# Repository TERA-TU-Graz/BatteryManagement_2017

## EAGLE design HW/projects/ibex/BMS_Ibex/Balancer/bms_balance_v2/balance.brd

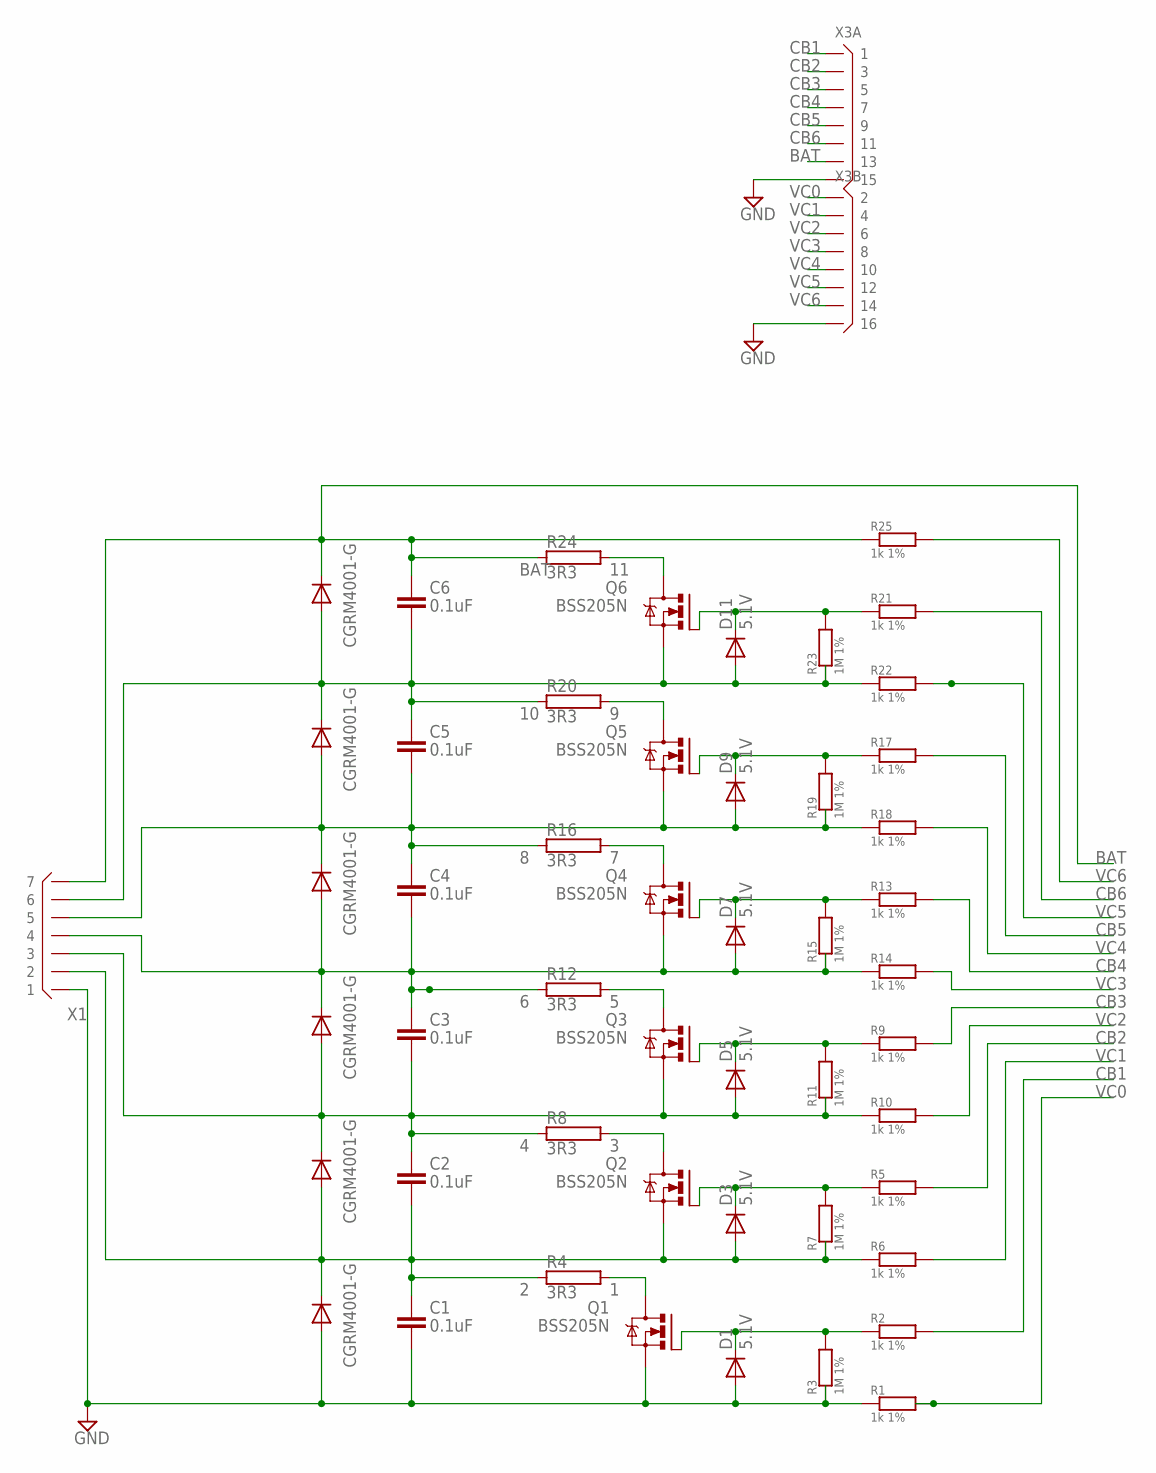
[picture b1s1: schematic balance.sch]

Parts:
C1, C2, C3, C4, C5, C6: 0.1uF; C0805
D1, D3, D5, D7, D9, D11: 5.1V; SOD-323
D2, D4, D6, D8, D10, D12: CGRM4001-G; SOD-123_MINI-SMA
Q1, Q2, Q3, Q4, Q5, Q6: BSS205N; SOT23
R1, R2, R5, R6, R9, R10, R13, R14, R17, R18, R21, R22, R25: 1k 1%; R0805
R3, R7, R11, R15, R19, R23: 1M 1%; R0805
R4, R8, R12, R16, R20, R24: 3R3; HS15
X1: B7B-XH
X3: X08X2DR; X16R-DIL

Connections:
1: Q1.3 (D), R4.2
2: C1.2, C2.1, D2.C, D3.2 (A), D4.A, Q2.2 (S), R4.1, R6.1, R7.1, X1.P$2 (2)
3: Q2.3 (D), R8.2
4: C2.2, C3.1, D4.C, D5.2 (A), D6.A, Q3.2 (S), R8.1, R10.1, R11.1, X1.P$3 (3)
5: Q3.3 (D), R12.2
6: C3.2, C4.1, D6.C, D7.2 (A), D8.A, Q4.2 (S), R12.1, R14.1, R15.1, X1.P$4 (4)
7: Q4.3 (D), R16.2
8: C4.2, C5.1, D8.C, D9.2 (A), D10.A, Q5.2 (S), R16.1, R18.1, R19.1, X1.P$5 (5)
9: Q5.3 (D), R20.2
10: C5.2, C6.1, D10.C, D11.2 (A), D12.A, Q6.2 (S), R20.1, R22.1, R23.1, X1.P$6 (6)
11: Q6.3 (D), R24.2
BAT: C6.2, D12.C, R24.1, R25.1, X1.P$7 (7), X3.13
CB1: R2.2, X3.1
CB2: R5.2, X3.3
CB3: R9.2, X3.5
CB4: R13.2, X3.7
CB5: R17.2, X3.9
CB6: R21.2, X3.11
GND: C1.1, D1.2 (A), D2.A, Q1.2 (S), R1.1, R3.1, X1.P$1 (1), X3.15, X3.16
unnamed: D1.1 (C), Q1.1 (G), R2.1, R3.2
unnamed: D3.1 (C), Q2.1 (G), R5.1, R7.2
unnamed: D5.1 (C), Q3.1 (G), R9.1, R11.2
unnamed: D7.1 (C), Q4.1 (G), R13.1, R15.2
unnamed: D9.1 (C), Q5.1 (G), R17.1, R19.2
unnamed: D11.1 (C), Q6.1 (G), R21.1, R23.2
VC0: R1.2, X3.2
VC1: R6.2, X3.4
VC2: R10.2, X3.6
VC3: R14.2, X3.8
VC4: R18.2, X3.10
VC5: R22.2, X3.12
VC6: R25.2, X3.14

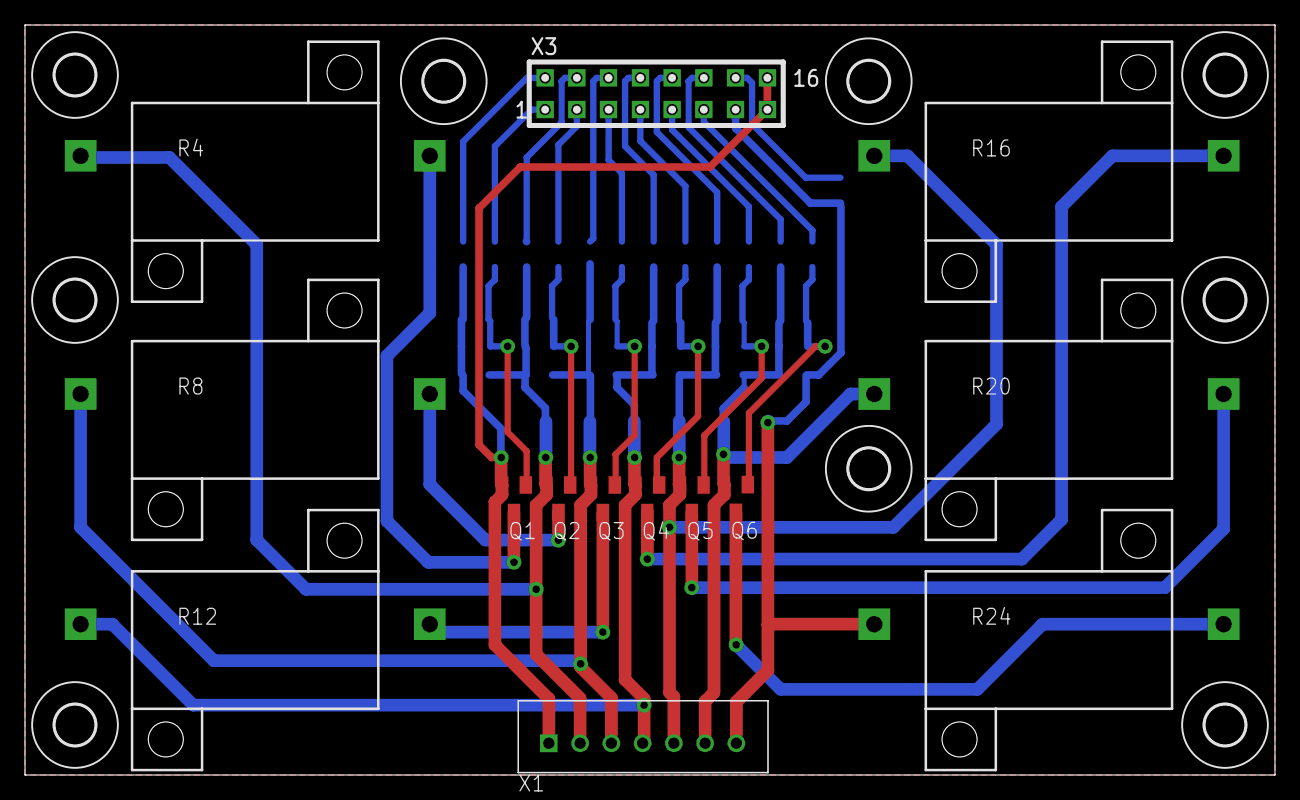
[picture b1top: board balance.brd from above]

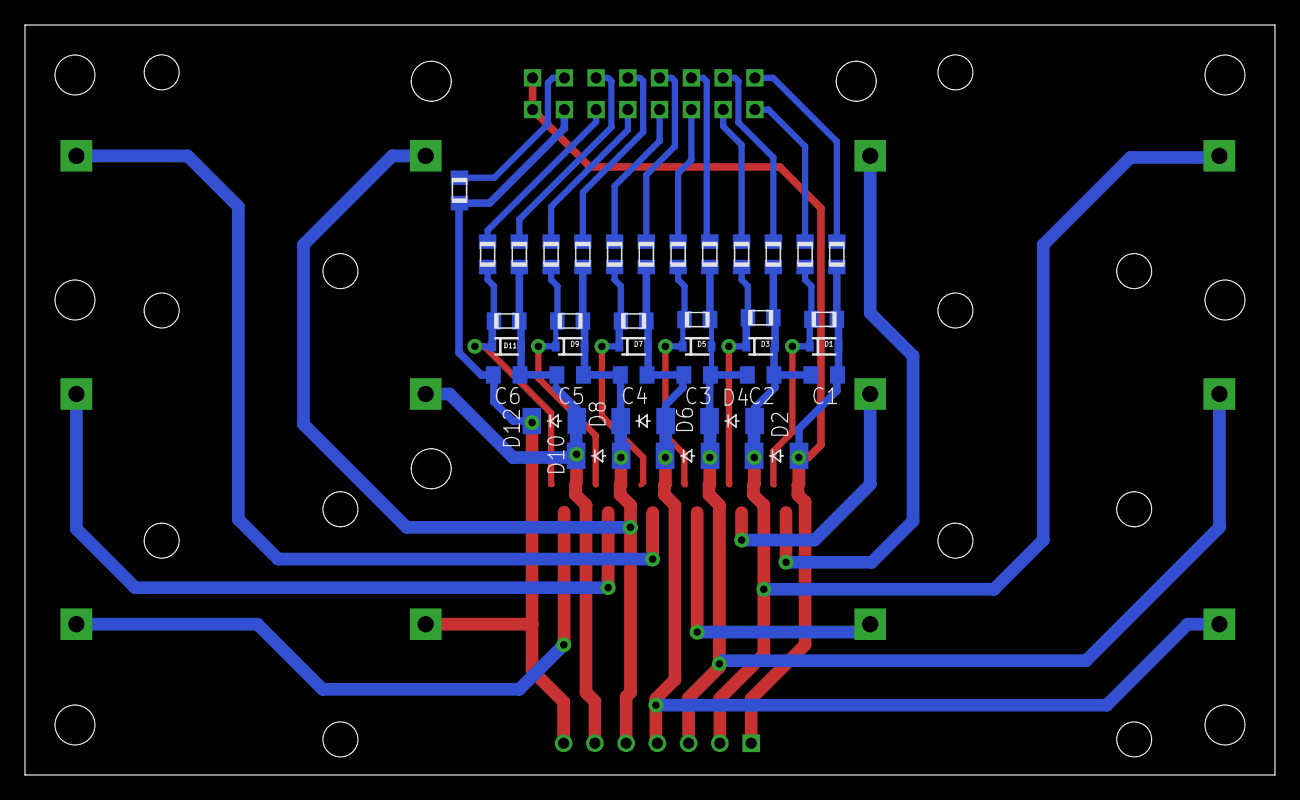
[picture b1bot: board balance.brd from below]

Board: 4 copper layers, 100.0 x 60.0 mm, 60 parts (37 on the bottom side), 32 nets.

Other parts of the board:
U$1, U$2, U$3, U$4, U$5, U$6, U$7, U$8, U$9: 3,2

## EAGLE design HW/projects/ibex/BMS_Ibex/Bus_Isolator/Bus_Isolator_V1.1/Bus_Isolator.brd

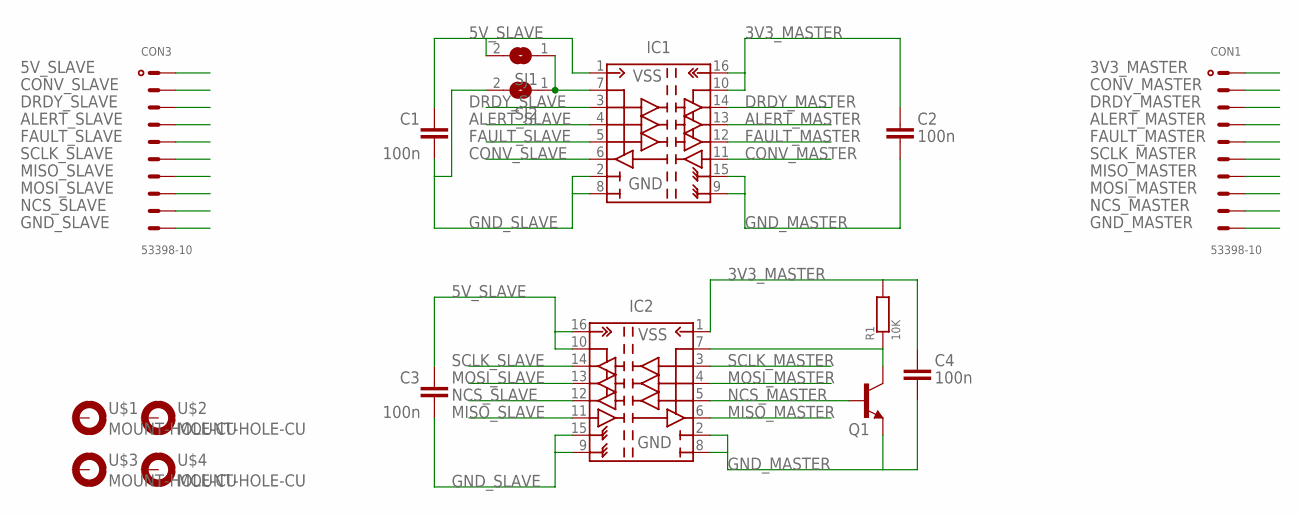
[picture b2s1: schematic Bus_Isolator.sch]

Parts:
C1, C2, C3, C4: 100n; C0805
CON1, CON3: 53398-10
IC1, IC2: ISO7241; R-PDSO-G16
Q1: TRANSISTOR_NPNSOT23; SOT23
R1: 10K; R0805
SJ1, SJ2: SJ
U$1, U$2, U$3, U$4: MOUNT-HOLE-CU; BOHRUNG-3,2-NUR-KUPFER

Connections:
3V3_MASTER: C2.2, C4.2, CON1.1, IC1.10 (EN2), IC1.16 (VCC2), IC2.1 (VCC1), R1.2
5V_SLAVE: C1.2, C3.2, CON3.1, IC1.1 (VCC1), IC2.10 (EN2), IC2.16 (VCC2), SJ1.2
ALERT_MASTER: CON1.4, IC1.13 (OUT_B)
ALERT_SLAVE: CON3.4, IC1.4 (IN_B)
CONV_MASTER: CON1.2, IC1.11 (IN_D)
CONV_SLAVE: CON3.2, IC1.6 (OUT_D)
DRDY_MASTER: CON1.3, IC1.14 (OUT_A)
DRDY_SLAVE: CON3.3, IC1.3 (IN_A)
FAULT_MASTER: CON1.5, IC1.12 (OUT_C)
FAULT_SLAVE: CON3.5, IC1.5 (IN_C)
GND_MASTER: C2.1, C4.1, CON1.10, IC1.9 (GND22), IC1.15 (GND21), IC2.2 (GND11), IC2.8 (GND12), Q1.2 (E)
GND_SLAVE: C1.1, C3.1, CON3.10, IC1.2 (GND11), IC1.8 (GND12), IC2.9 (GND22), IC2.15 (GND21), SJ2.2
MISO_MASTER: CON1.7, IC2.6 (OUT_D)
MISO_SLAVE: CON3.7, IC2.11 (IN_D)
MOSI_MASTER: CON1.8, IC2.4 (IN_B)
MOSI_SLAVE: CON3.8, IC2.13 (OUT_B)
unnamed: IC1.7 (EN1), SJ1.1, SJ2.1
unnamed: IC2.7 (EN1), Q1.3 (C), R1.1
NCS_MASTER: CON1.9, IC2.5 (IN_C), Q1.1 (B)
NCS_SLAVE: CON3.9, IC2.12 (OUT_C)
SCLK_MASTER: CON1.6, IC2.3 (IN_A)
SCLK_SLAVE: CON3.6, IC2.14 (OUT_A)

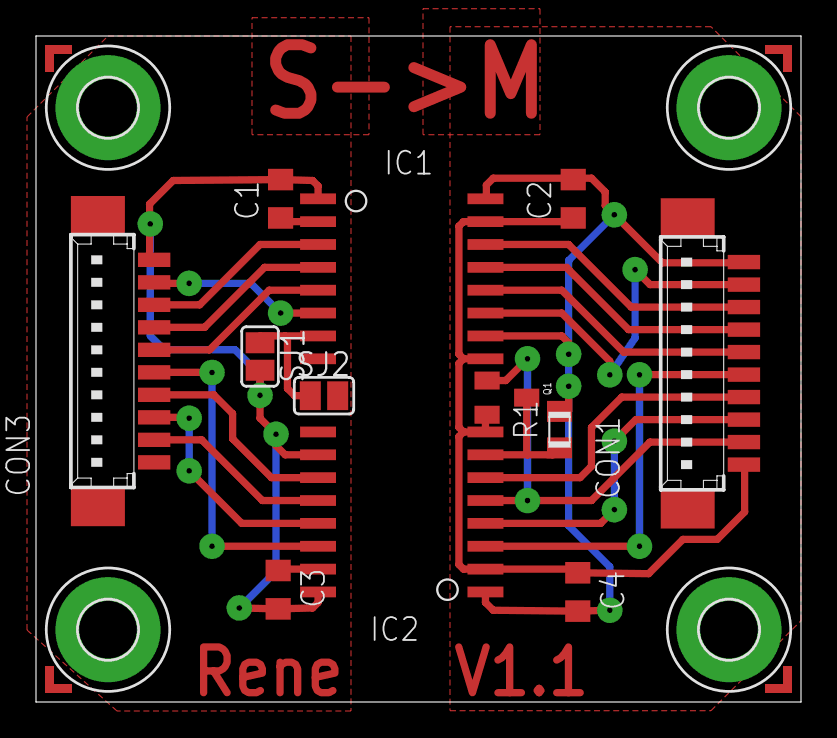
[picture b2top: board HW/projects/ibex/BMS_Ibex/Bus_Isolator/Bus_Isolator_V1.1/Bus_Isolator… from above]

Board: 2 copper layers, 42.5 x 37.0 mm, 16 parts (0 on the bottom side), 22 nets.

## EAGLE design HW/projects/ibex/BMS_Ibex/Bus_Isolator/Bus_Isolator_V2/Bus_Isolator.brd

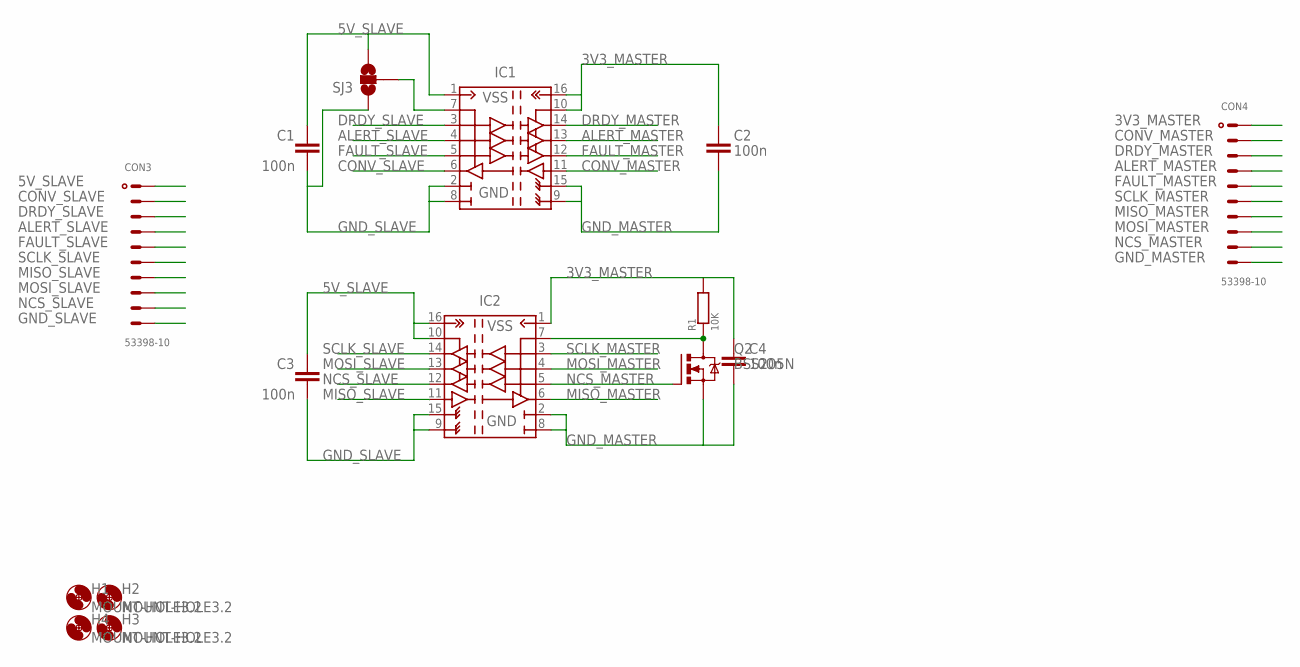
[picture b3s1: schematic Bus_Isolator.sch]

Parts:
C1, C2, C3, C4: 100n; C0805
CON3, CON4: 53398-10
H1, H2, H3, H4: MOUNT-HOLE3.2; 3,2
IC1, IC2: ISO7241; R-PDSO-G16
Q2: BSS205N; SOT23
R1: 10K; R0805
SJ3: SOLDERJUMPER_2WAYS; SJ_3

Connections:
3V3_MASTER: C2.2, C4.2, CON4.1, IC1.10 (EN2), IC1.16 (VCC2), IC2.1 (VCC1), R1.2
5V_SLAVE: C1.2, C3.2, CON3.1, IC1.1 (VCC1), IC2.10 (EN2), IC2.16 (VCC2), SJ3.3
ALERT_MASTER: CON4.4, IC1.13 (OUT_B)
ALERT_SLAVE: CON3.4, IC1.4 (IN_B)
CONV_MASTER: CON4.2, IC1.11 (IN_D)
CONV_SLAVE: CON3.2, IC1.6 (OUT_D)
DRDY_MASTER: CON4.3, IC1.14 (OUT_A)
DRDY_SLAVE: CON3.3, IC1.3 (IN_A)
FAULT_MASTER: CON4.5, IC1.12 (OUT_C)
FAULT_SLAVE: CON3.5, IC1.5 (IN_C)
GND_MASTER: C2.1, C4.1, CON4.10, IC1.9 (GND22), IC1.15 (GND21), IC2.2 (GND11), IC2.8 (GND12), Q2.2 (S)
GND_SLAVE: C1.1, C3.1, CON3.10, IC1.2 (GND11), IC1.8 (GND12), IC2.9 (GND22), IC2.15 (GND21), SJ3.1
MISO_MASTER: CON4.7, IC2.6 (OUT_D)
MISO_SLAVE: CON3.7, IC2.11 (IN_D)
MOSI_MASTER: CON4.8, IC2.4 (IN_B)
MOSI_SLAVE: CON3.8, IC2.13 (OUT_B)
unnamed: IC1.7 (EN1), SJ3.2
unnamed: IC2.7 (EN1), Q2.3 (D), R1.1
NCS_MASTER: CON4.9, IC2.5 (IN_C), Q2.1 (G)
NCS_SLAVE: CON3.9, IC2.12 (OUT_C)
SCLK_MASTER: CON4.6, IC2.3 (IN_A)
SCLK_SLAVE: CON3.6, IC2.14 (OUT_A)

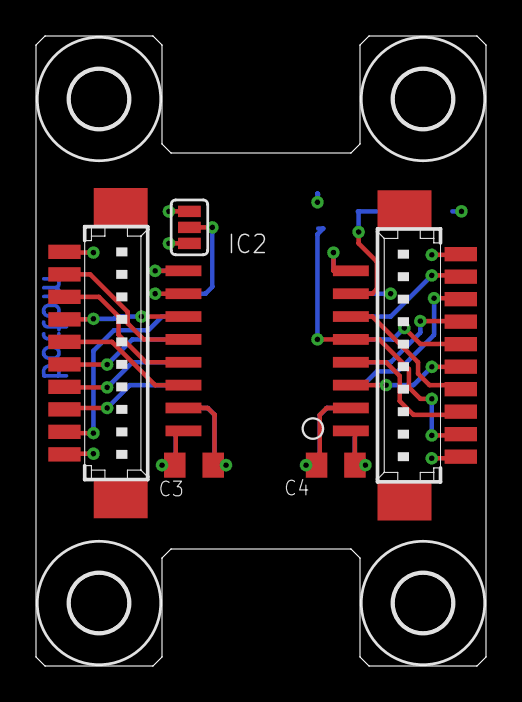
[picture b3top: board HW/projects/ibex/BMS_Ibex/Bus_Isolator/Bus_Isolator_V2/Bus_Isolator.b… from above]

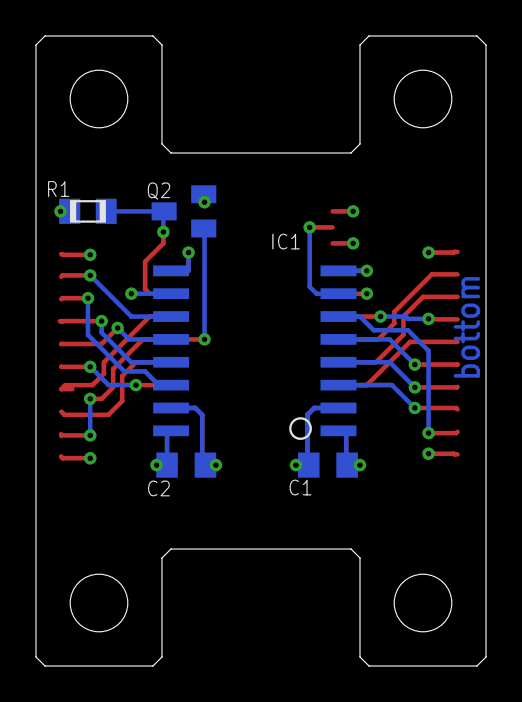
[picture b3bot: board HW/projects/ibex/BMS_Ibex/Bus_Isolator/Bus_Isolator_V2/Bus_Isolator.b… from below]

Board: 4 copper layers, 25.0 x 35.0 mm, 15 parts (5 on the bottom side), 22 nets.

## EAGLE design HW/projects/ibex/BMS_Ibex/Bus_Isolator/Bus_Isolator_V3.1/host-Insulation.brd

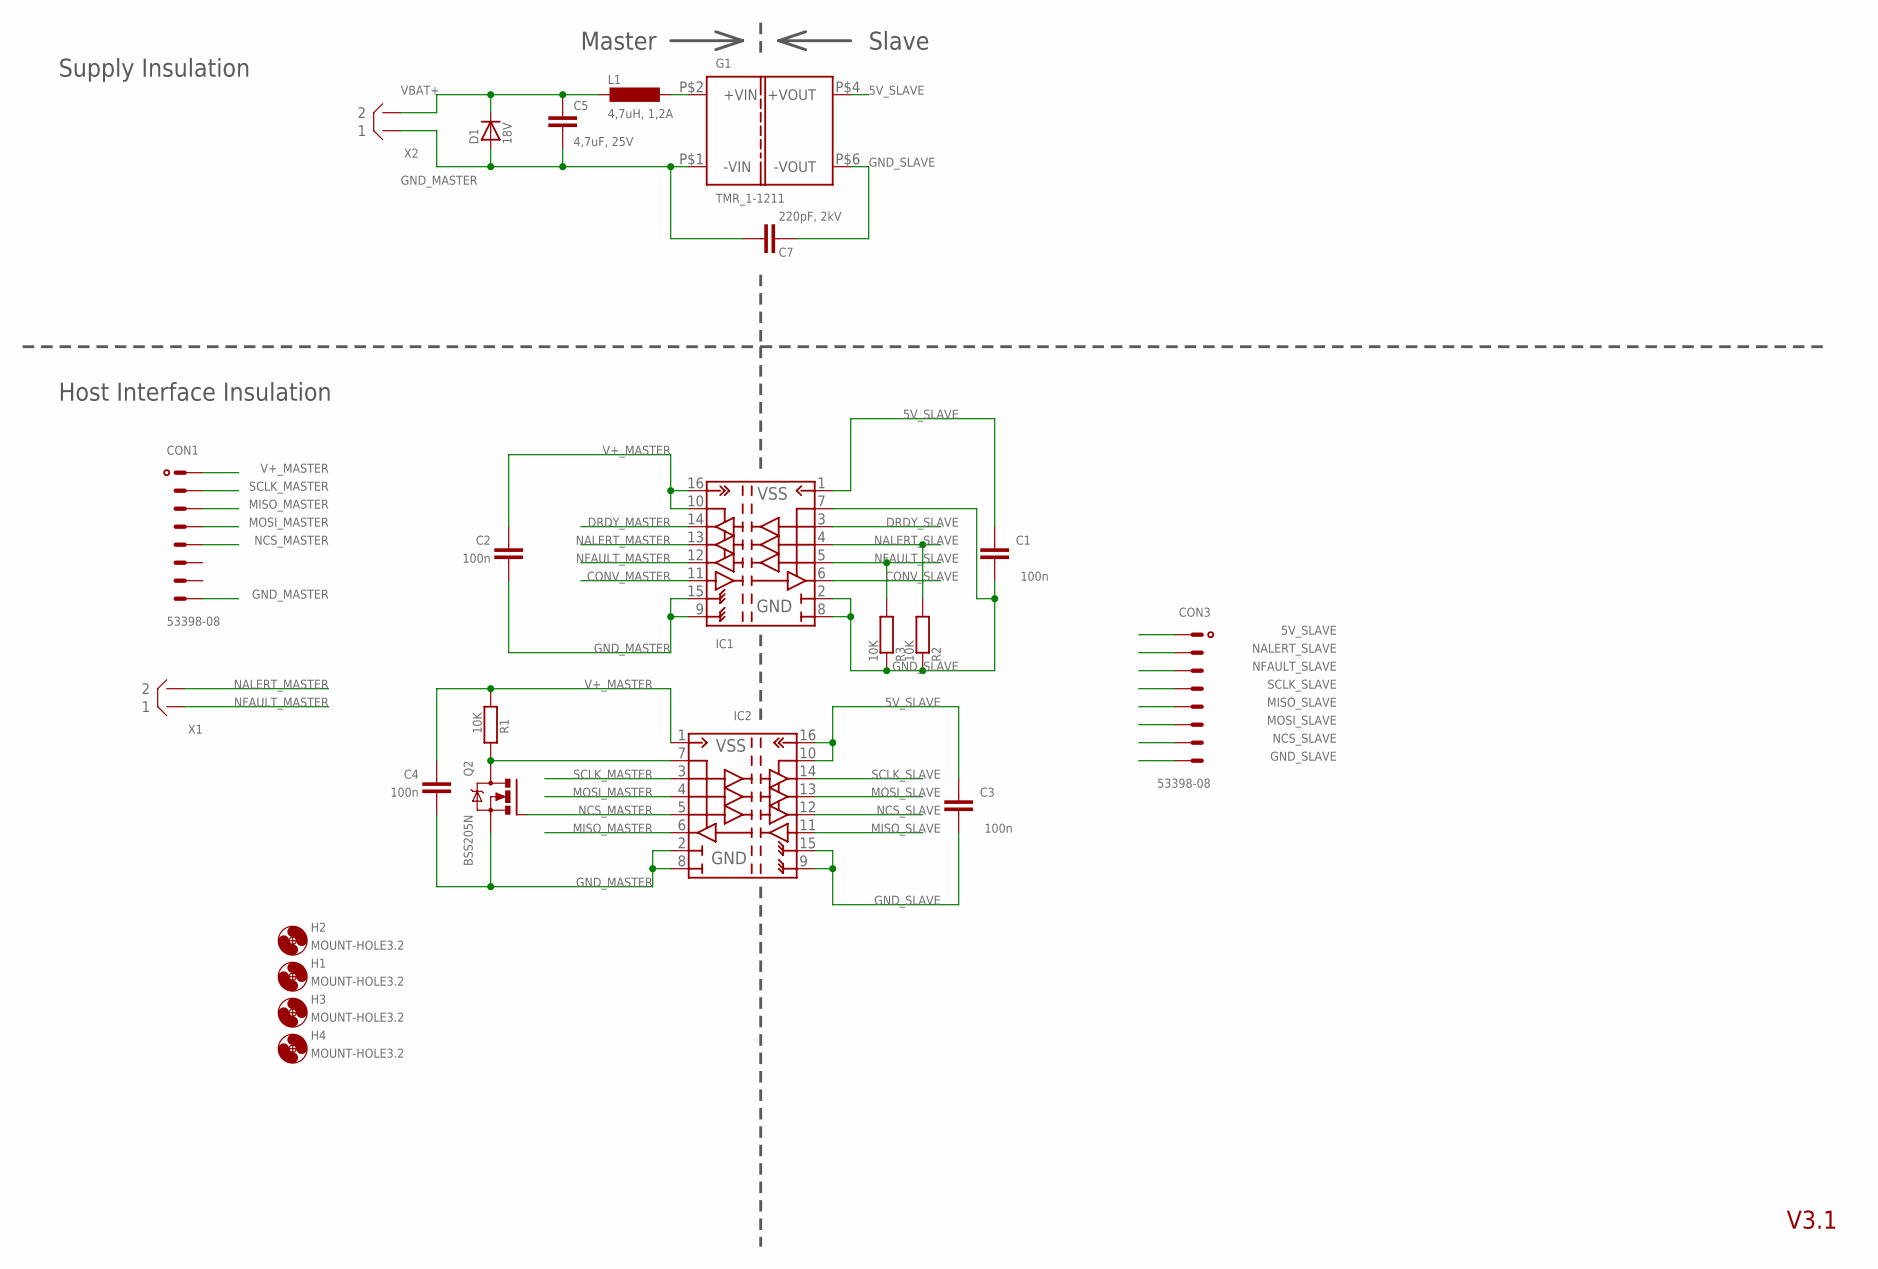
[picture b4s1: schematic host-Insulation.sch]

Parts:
C1, C2, C3, C4: 100n; C0805
C5: 4,7uF, 25V; C0805
C7: 220pF, 2kV; C1210_HV
CON1, CON3: 53398-08
D1: 18V; DO214AA
G1: TMR_1-1211; TMR_1-??1?
H1, H2, H3, H4: MOUNT-HOLE3.2; 3,2
IC1, IC2: ISO7241; R-PDSO-G16
L1: 4,7uH, 1,2A; L3225M
Q2: BSS205N; SOT23
R1, R2, R3: 10K; R0805
X1, X2: B2B-XH

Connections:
5V_SLAVE: C1.2, C3.2, CON3.1, G1.P$4 (+VOUT), IC1.1 (VCC1), IC2.10 (EN2), IC2.16 (VCC2)
CONV_MASTER: IC1.11 (IN_D)
CONV_SLAVE: IC1.6 (OUT_D)
DRDY_MASTER: IC1.14 (OUT_A)
DRDY_SLAVE: IC1.3 (IN_A)
GND_MASTER: C2.1, C4.1, C5.2, C7.P$1 (1), CON1.8, D1.A, G1.P$1 (-VIN), IC1.9 (GND22), IC1.15 (GND21), IC2.2 (GND11), IC2.8 (GND12), Q2.2 (S), X2.P$1 (1)
GND_SLAVE: C1.1, C3.1, C7.P$2 (2), CON3.8, G1.P$6 (-VOUT), IC1.2 (GND11), IC1.7 (EN1), IC1.8 (GND12), IC2.9 (GND22), IC2.15 (GND21), R2.1, R3.1
MISO_MASTER: CON1.3, IC2.6 (OUT_D)
MISO_SLAVE: CON3.5, IC2.11 (IN_D)
MOSI_MASTER: CON1.4, IC2.4 (IN_B)
MOSI_SLAVE: CON3.6, IC2.13 (OUT_B)
unnamed: IC2.7 (EN1), Q2.3 (D), R1.1
unnamed: G1.P$2 (+VIN), L1.1
NALERT_MASTER: IC1.13 (OUT_B), X1.P$2 (2)
NALERT_SLAVE: CON3.2, IC1.4 (IN_B), R2.2
NCS_MASTER: CON1.5, IC2.5 (IN_C), Q2.1 (G)
NCS_SLAVE: CON3.7, IC2.12 (OUT_C)
NFAULT_MASTER: IC1.12 (OUT_C), X1.P$1 (1)
NFAULT_SLAVE: CON3.3, IC1.5 (IN_C), R3.2
SCLK_MASTER: CON1.2, IC2.3 (IN_A)
SCLK_SLAVE: CON3.4, IC2.14 (OUT_A)
V+_MASTER: C2.2, C4.2, CON1.1, IC1.10 (EN2), IC1.16 (VCC2), IC2.1 (VCC1), R1.2
VBAT+: C5.1, D1.C, L1.2, X2.P$2 (2)

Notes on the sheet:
V3.1
Supply Insulation
Host Interface Insulation
Master
Slave

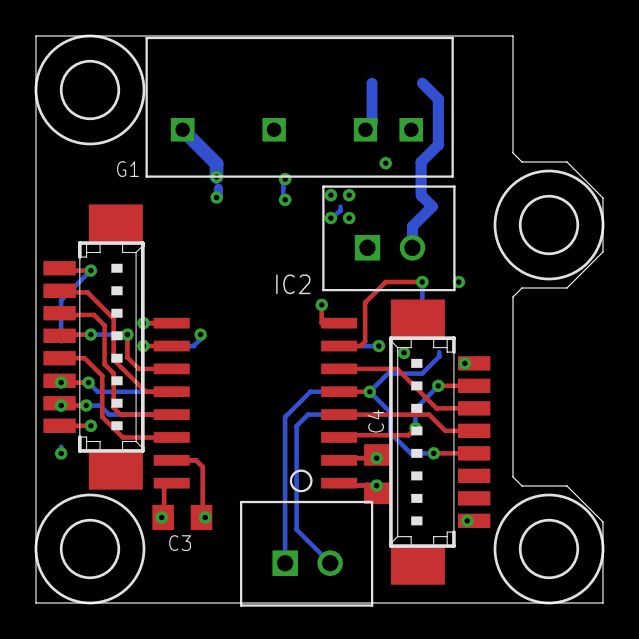
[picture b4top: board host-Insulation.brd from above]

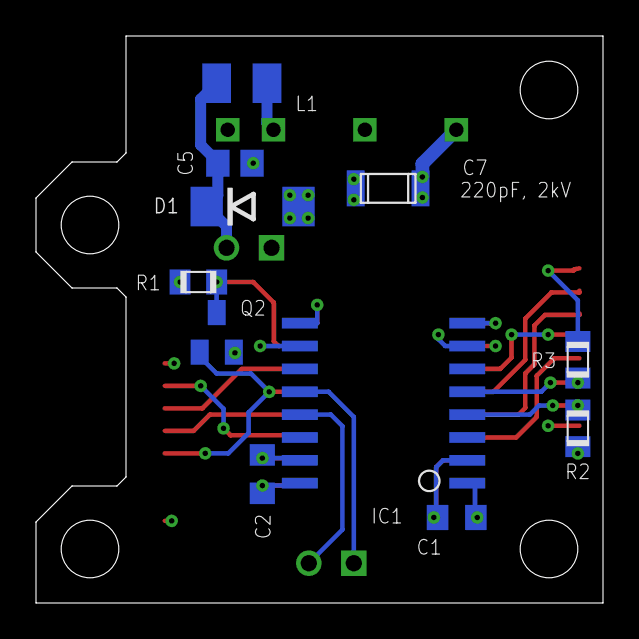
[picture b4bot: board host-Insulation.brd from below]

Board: 4 copper layers, 31.5 x 31.5 mm, 23 parts (11 on the bottom side), 19 nets.

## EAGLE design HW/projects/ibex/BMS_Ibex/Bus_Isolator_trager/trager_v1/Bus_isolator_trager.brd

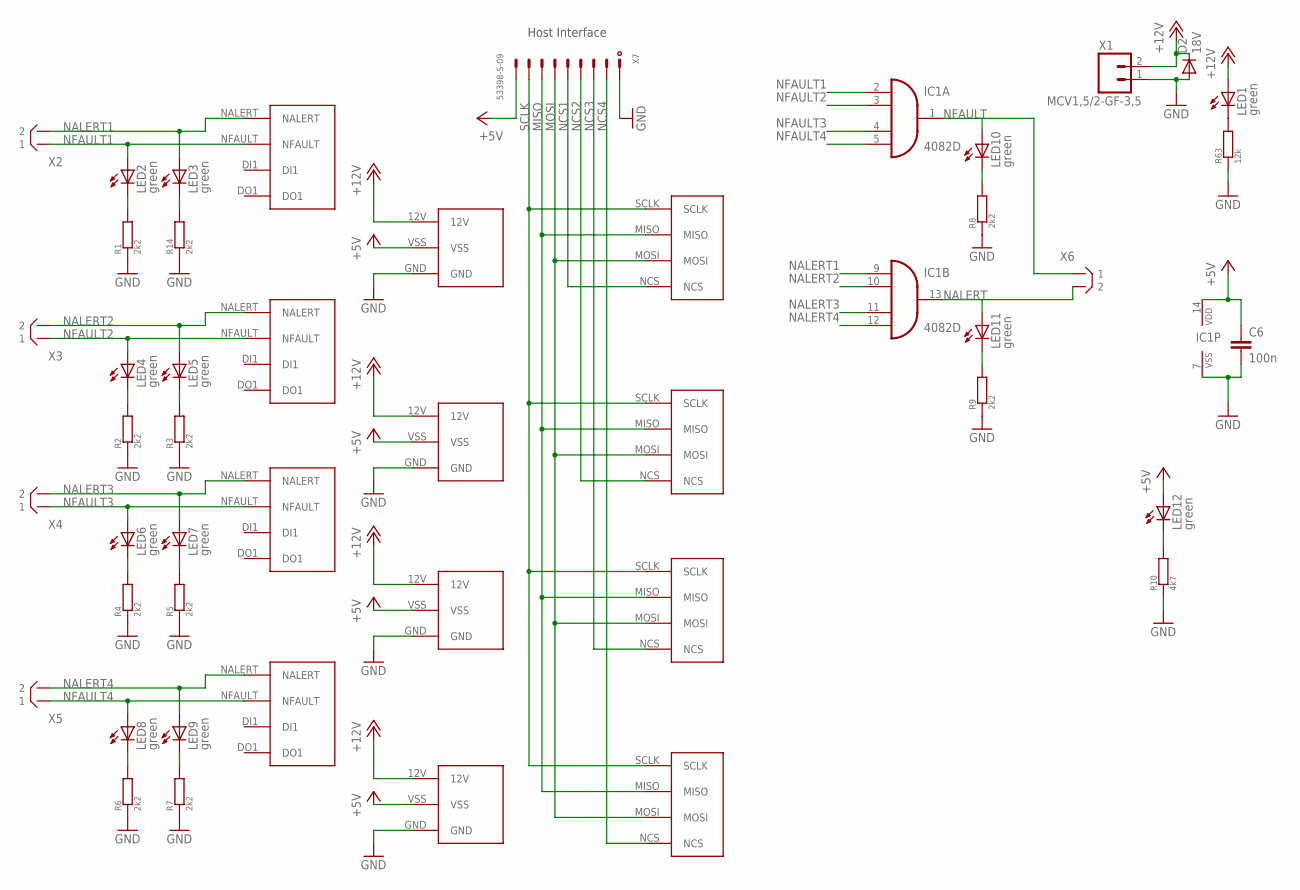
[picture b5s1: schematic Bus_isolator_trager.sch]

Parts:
A1, A2, A3, A4: SPI_ISOLATOR_V4
C6: 100n; C0603
D2: 18V; DO214AA
IC1: 4082D; SO14
LED1, LED12: green; CHIP-LED0805
LED2, LED3, LED4, LED5, LED6, LED7, LED8, LED9, LED10, LED11: green; CHIPLED_0805
R1, R2, R3, R4, R5, R6, R7, R8, R9, R14: 2k2; R0603
R10: 4k7; R0603
R63: 12k; R0603
X1: MCV1,5/2-GF-3,5
X2, X3, X4, X5, X6: B2B-XH
X7: 53398-S-09; 53398-09-S

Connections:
+5V: A1.VSS, A2.VSS, A3.VSS, A4.VSS, C6.1, IC1.14 (VDD), LED12.A, X7.9
+12V: A1.12V, A2.12V, A3.12V, A4.12V, D2.C, LED1.A, X1.2
GND: A1.GND, A2.GND, A3.GND, A4.GND, C6.2, D2.A, IC1.7 (VSS), R1.1, R2.1, R3.1, R4.1, R5.1, R6.1, R7.1, R8.1, R9.1, R10.1, R14.1, R63.1, X1.1, X7.1
MISO: A1.MISO, A2.MISO, A3.MISO, A4.MISO, X7.7
MOSI: A1.MOSI, A2.MOSI, A3.MOSI, A4.MOSI, X7.6
unnamed: LED2.C, R1.2
unnamed: LED4.C, R2.2
unnamed: LED5.C, R3.2
unnamed: LED6.C, R4.2
unnamed: LED7.C, R5.2
unnamed: LED8.C, R6.2
unnamed: LED9.C, R7.2
unnamed: LED10.C, R8.2
unnamed: LED11.C, R9.2
unnamed: LED12.C, R10.2
unnamed: LED3.C, R14.2
unnamed: LED1.C, R63.2
NALERT: IC1.13 (O), LED11.A, X6.P$2 (2)
NALERT1: A1.NALERT, IC1.9 (I0), LED3.A, X2.P$2 (2)
NALERT2: A2.NALERT, IC1.10 (I1), LED5.A, X3.P$2 (2)
NALERT3: A3.NALERT, IC1.11 (I2), LED7.A, X4.P$2 (2)
NALERT4: A4.NALERT, IC1.12 (I3), LED9.A, X5.P$2 (2)
NCS1: A1.NCS, X7.5
NCS2: A2.NCS, X7.4
NCS3: A3.NCS, X7.3
NCS4: A4.NCS, X7.2
NFAULT: IC1.1 (O), LED10.A, X6.P$1 (1)
NFAULT1: A1.NFAULT, IC1.2 (I0), LED2.A, X2.P$1 (1)
NFAULT2: A2.NFAULT, IC1.3 (I1), LED4.A, X3.P$1 (1)
NFAULT3: A3.NFAULT, IC1.4 (I2), LED6.A, X4.P$1 (1)
NFAULT4: A4.NFAULT, IC1.5 (I3), LED8.A, X5.P$1 (1)
SCLK: A1.SCLK, A2.SCLK, A3.SCLK, A4.SCLK, X7.8

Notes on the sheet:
Host Interface

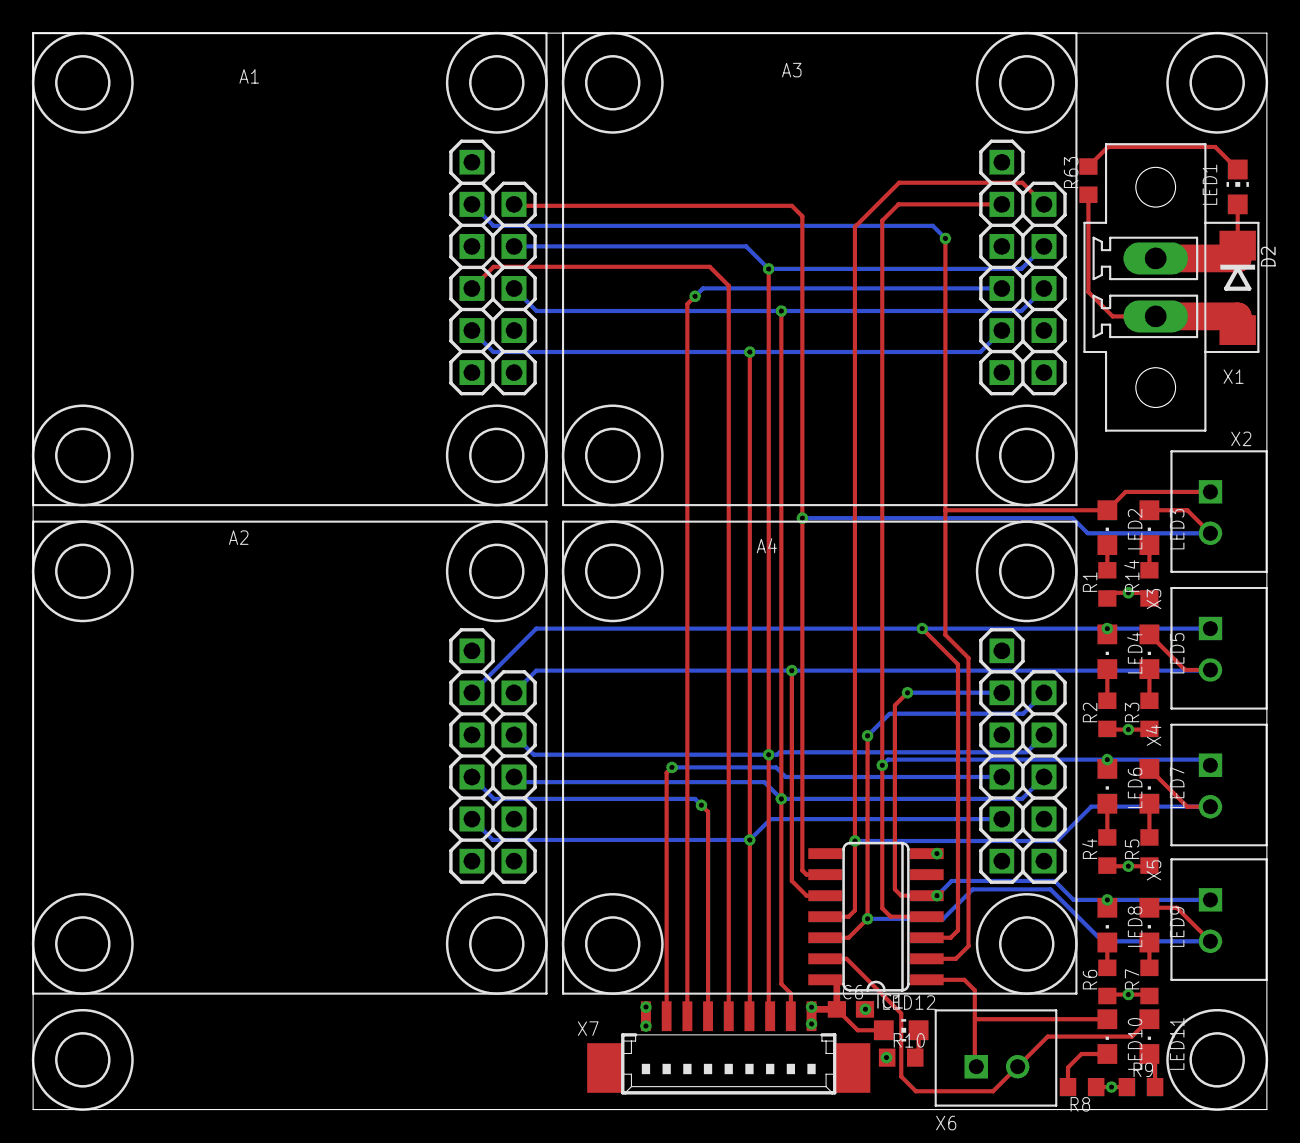
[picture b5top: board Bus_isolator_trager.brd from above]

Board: 4 copper layers, 74.5 x 65.0 mm, 41 parts (0 on the bottom side), 32 nets.

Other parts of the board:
U$5, U$7, U$8: 3,2

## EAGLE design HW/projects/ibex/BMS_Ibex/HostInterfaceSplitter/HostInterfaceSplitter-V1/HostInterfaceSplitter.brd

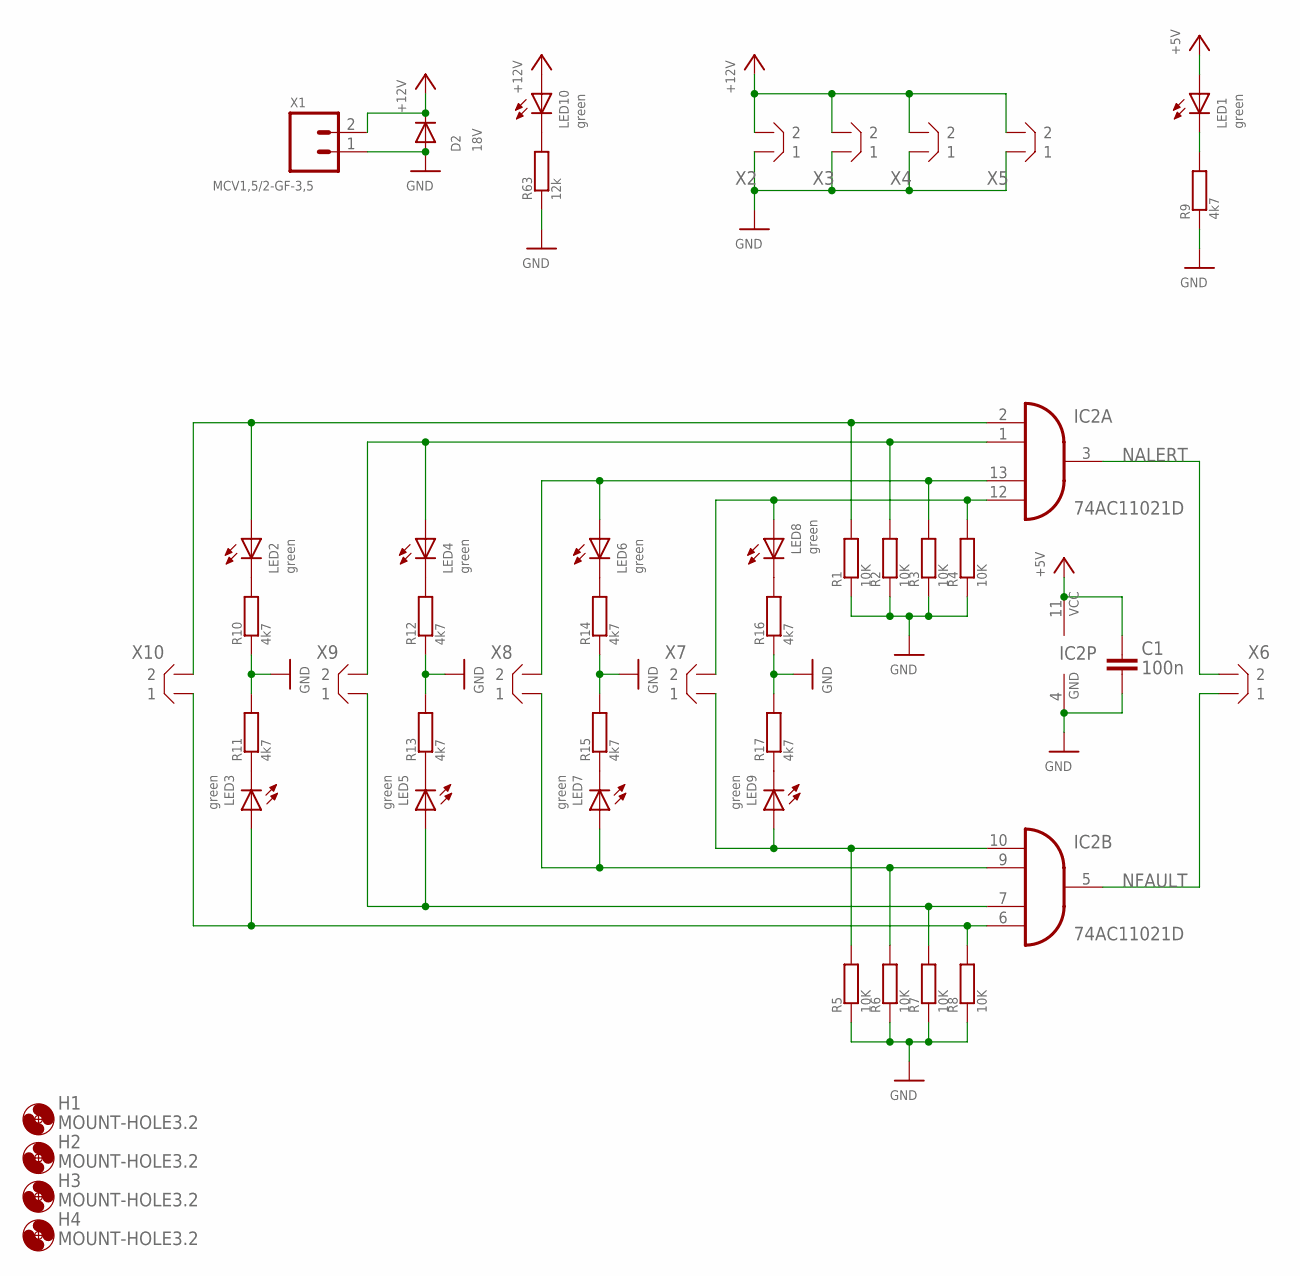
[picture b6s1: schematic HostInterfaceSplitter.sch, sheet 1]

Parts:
C1: 100n; C0603
D2: 18V; DO214AA
H1, H2, H3, H4: MOUNT-HOLE3.2; 3,2
IC2: 74AC11021D; SO14
LED1, LED2, LED3, LED4, LED5, LED6, LED7, LED8, LED9, LED10: green; CHIP-LED0805
R1, R2, R3, R4, R5, R6, R7, R8: 10K; R0603
R9, R10, R11, R12, R13, R14, R15, R16, R17: 4k7; R0805
R63: 12k; R0805
X1: MCV1,5/2-GF-3,5
X2, X3, X4, X5, X6, X7, X8, X9, X10: B2B-XH

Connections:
+5V: C1.2, IC2.11 (VCC), LED1.A; also elsewhere on the board
+12V: D2.C, LED10.A, X1.2, X2.P$2 (2), X3.P$2 (2), X4.P$2 (2), X5.P$2 (2)
GND: C1.1, D2.A, IC2.4 (GND), R1.1, R2.1, R3.1, R4.1, R5.1, R6.1, R7.1, R8.1, R9.1, R10.1, R11.2, R12.1, R13.2, R14.1, R15.2, R16.1, R17.2, R63.1, X1.1, X2.P$1 (1), X3.P$1 (1), X4.P$1 (1), X5.P$1 (1); also elsewhere on the board
unnamed: IC2.6 (I3), LED3.A, R8.2, X10.P$1 (1)
unnamed: IC2.12 (I3), LED8.A, R4.2, X7.P$2 (2)
unnamed: IC2.13 (I2), LED6.A, R3.2, X8.P$2 (2)
unnamed: IC2.1 (I1), LED4.A, R2.2, X9.P$2 (2)
unnamed: IC2.2 (I0), LED2.A, R1.2, X10.P$2 (2)
unnamed: IC2.7 (I2), LED5.A, R7.2, X9.P$1 (1)
unnamed: IC2.9 (I1), LED7.A, R6.2, X8.P$1 (1)
unnamed: IC2.10 (I0), LED9.A, R5.2, X7.P$1 (1)
unnamed: LED1.C, R9.2
unnamed: LED2.C, R10.2
unnamed: LED3.C, R11.1
unnamed: LED4.C, R12.2
unnamed: LED5.C, R13.1
unnamed: LED6.C, R14.2
unnamed: LED7.C, R15.1
unnamed: LED8.C, R16.2
unnamed: LED9.C, R17.1
unnamed: LED10.C, R63.2
NALERT: IC2.3 (O), X6.P$2 (2)
NFAULT: IC2.5 (O), X6.P$1 (1)

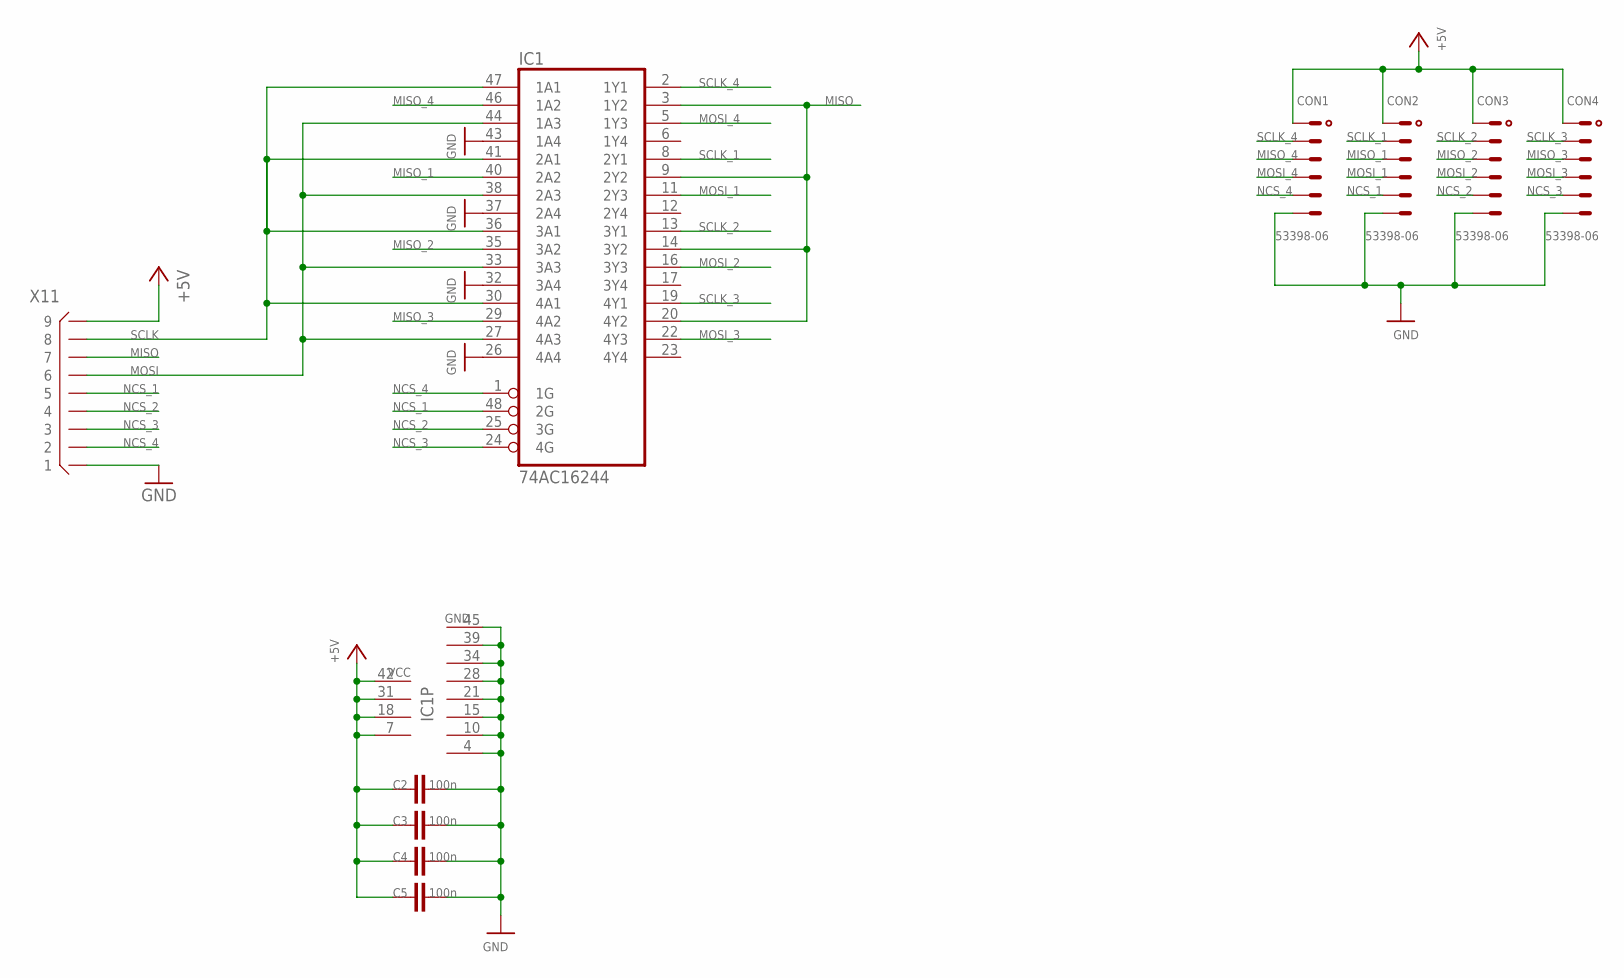
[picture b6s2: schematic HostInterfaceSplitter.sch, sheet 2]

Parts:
C2, C3, C4, C5: 100n; C0603
CON1, CON2, CON3, CON4: 53398-06
IC1: 74AC16244; SSOP48DL
X11: B9B-XH

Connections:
+5V: C2.2, C3.2, C4.2, C5.2, CON1.1, CON2.1, CON3.1, CON4.1, IC1.7 (VCC), IC1.18 (VCC), IC1.31 (VCC), IC1.42 (VCC), X11.P$9 (9); also elsewhere on the board
GND: C2.1, C3.1, C4.1, C5.1, CON1.6, CON2.6, CON3.6, CON4.6, IC1.4 (GND), IC1.10 (GND), IC1.15 (GND), IC1.21 (GND), IC1.26 (4A4), IC1.28 (GND), IC1.32 (3A4), IC1.34 (GND), IC1.37 (2A4), IC1.39 (GND), IC1.43 (1A4), IC1.45 (GND), X11.P$1 (1); also elsewhere on the board
MISO: IC1.3 (1Y2), IC1.9 (2Y2), IC1.14 (3Y2), IC1.20 (4Y2), X11.P$7 (7)
MISO_1: CON2.3, IC1.40 (2A2)
MISO_2: CON3.3, IC1.35 (3A2)
MISO_3: CON4.3, IC1.29 (4A2)
MISO_4: CON1.3, IC1.46 (1A2)
MOSI: IC1.27 (4A3), IC1.33 (3A3), IC1.38 (2A3), IC1.44 (1A3), X11.P$6 (6)
MOSI_1: CON2.4, IC1.11 (2Y3)
MOSI_2: CON3.4, IC1.16 (3Y3)
MOSI_3: CON4.4, IC1.22 (4Y3)
MOSI_4: CON1.4, IC1.5 (1Y3)
NCS_1: CON2.5, IC1.48 (2G), X11.P$5 (5)
NCS_2: CON3.5, IC1.25 (3G), X11.P$4 (4)
NCS_3: CON4.5, IC1.24 (4G), X11.P$3 (3)
NCS_4: CON1.5, IC1.1 (1G), X11.P$2 (2)
SCLK: IC1.30 (4A1), IC1.36 (3A1), IC1.41 (2A1), IC1.47 (1A1), X11.P$8 (8)
SCLK_1: CON2.2, IC1.8 (2Y1)
SCLK_2: CON3.2, IC1.13 (3Y1)
SCLK_3: CON4.2, IC1.19 (4Y1)
SCLK_4: CON1.2, IC1.2 (1Y1)

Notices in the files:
parts and their libraries:
SparkFun: Licensing: CC v3.0 Share-Alike You are welcome to use this library for commercial purposes.
